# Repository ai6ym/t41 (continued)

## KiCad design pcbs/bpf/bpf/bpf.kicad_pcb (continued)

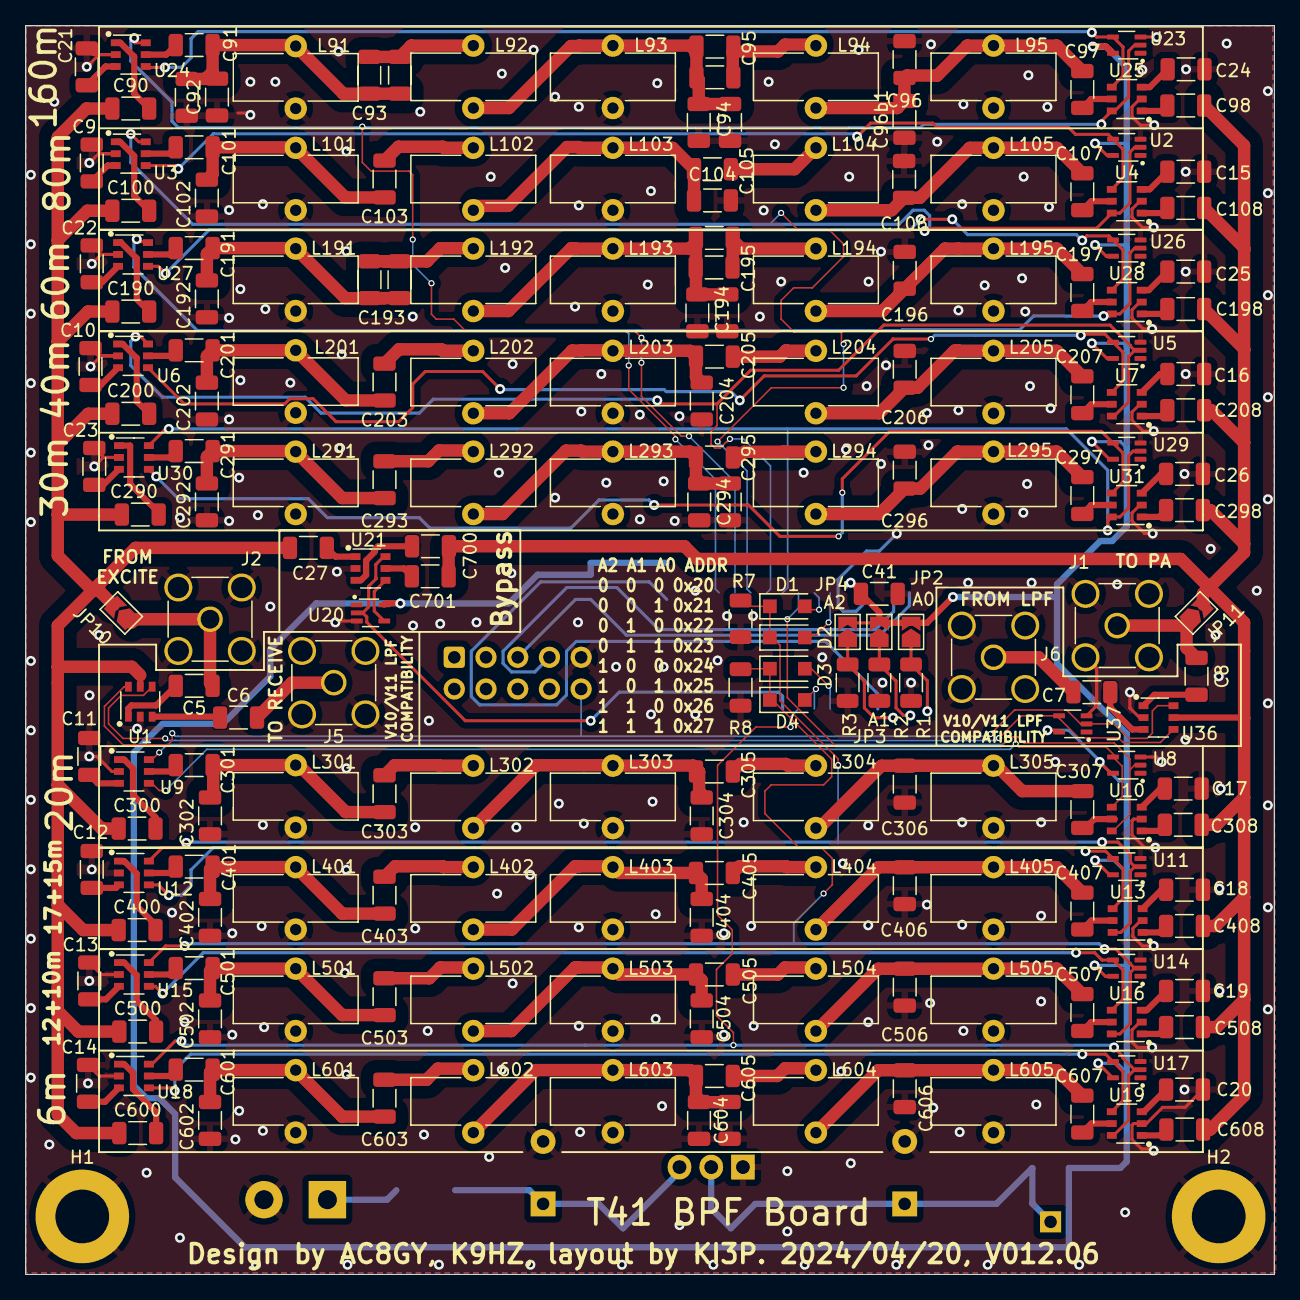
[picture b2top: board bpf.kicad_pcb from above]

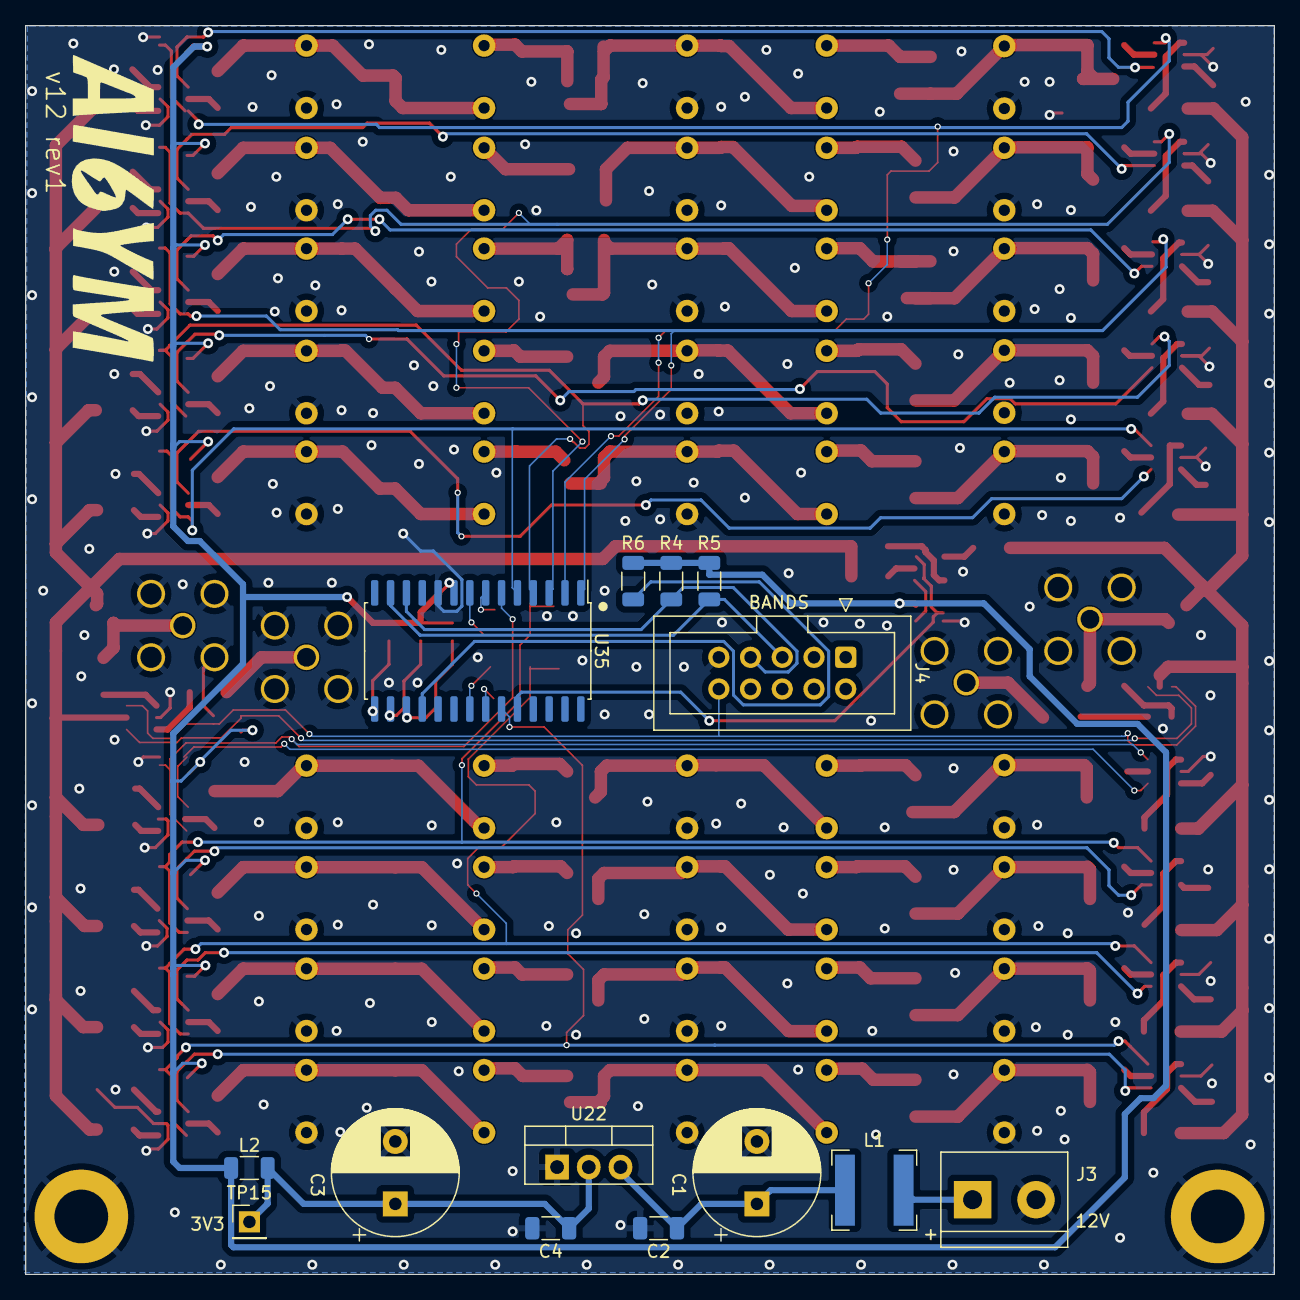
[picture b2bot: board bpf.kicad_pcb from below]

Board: 2 copper layers, 100.0 x 100.0 mm, 228 parts (14 on the bottom side), 149 nets.

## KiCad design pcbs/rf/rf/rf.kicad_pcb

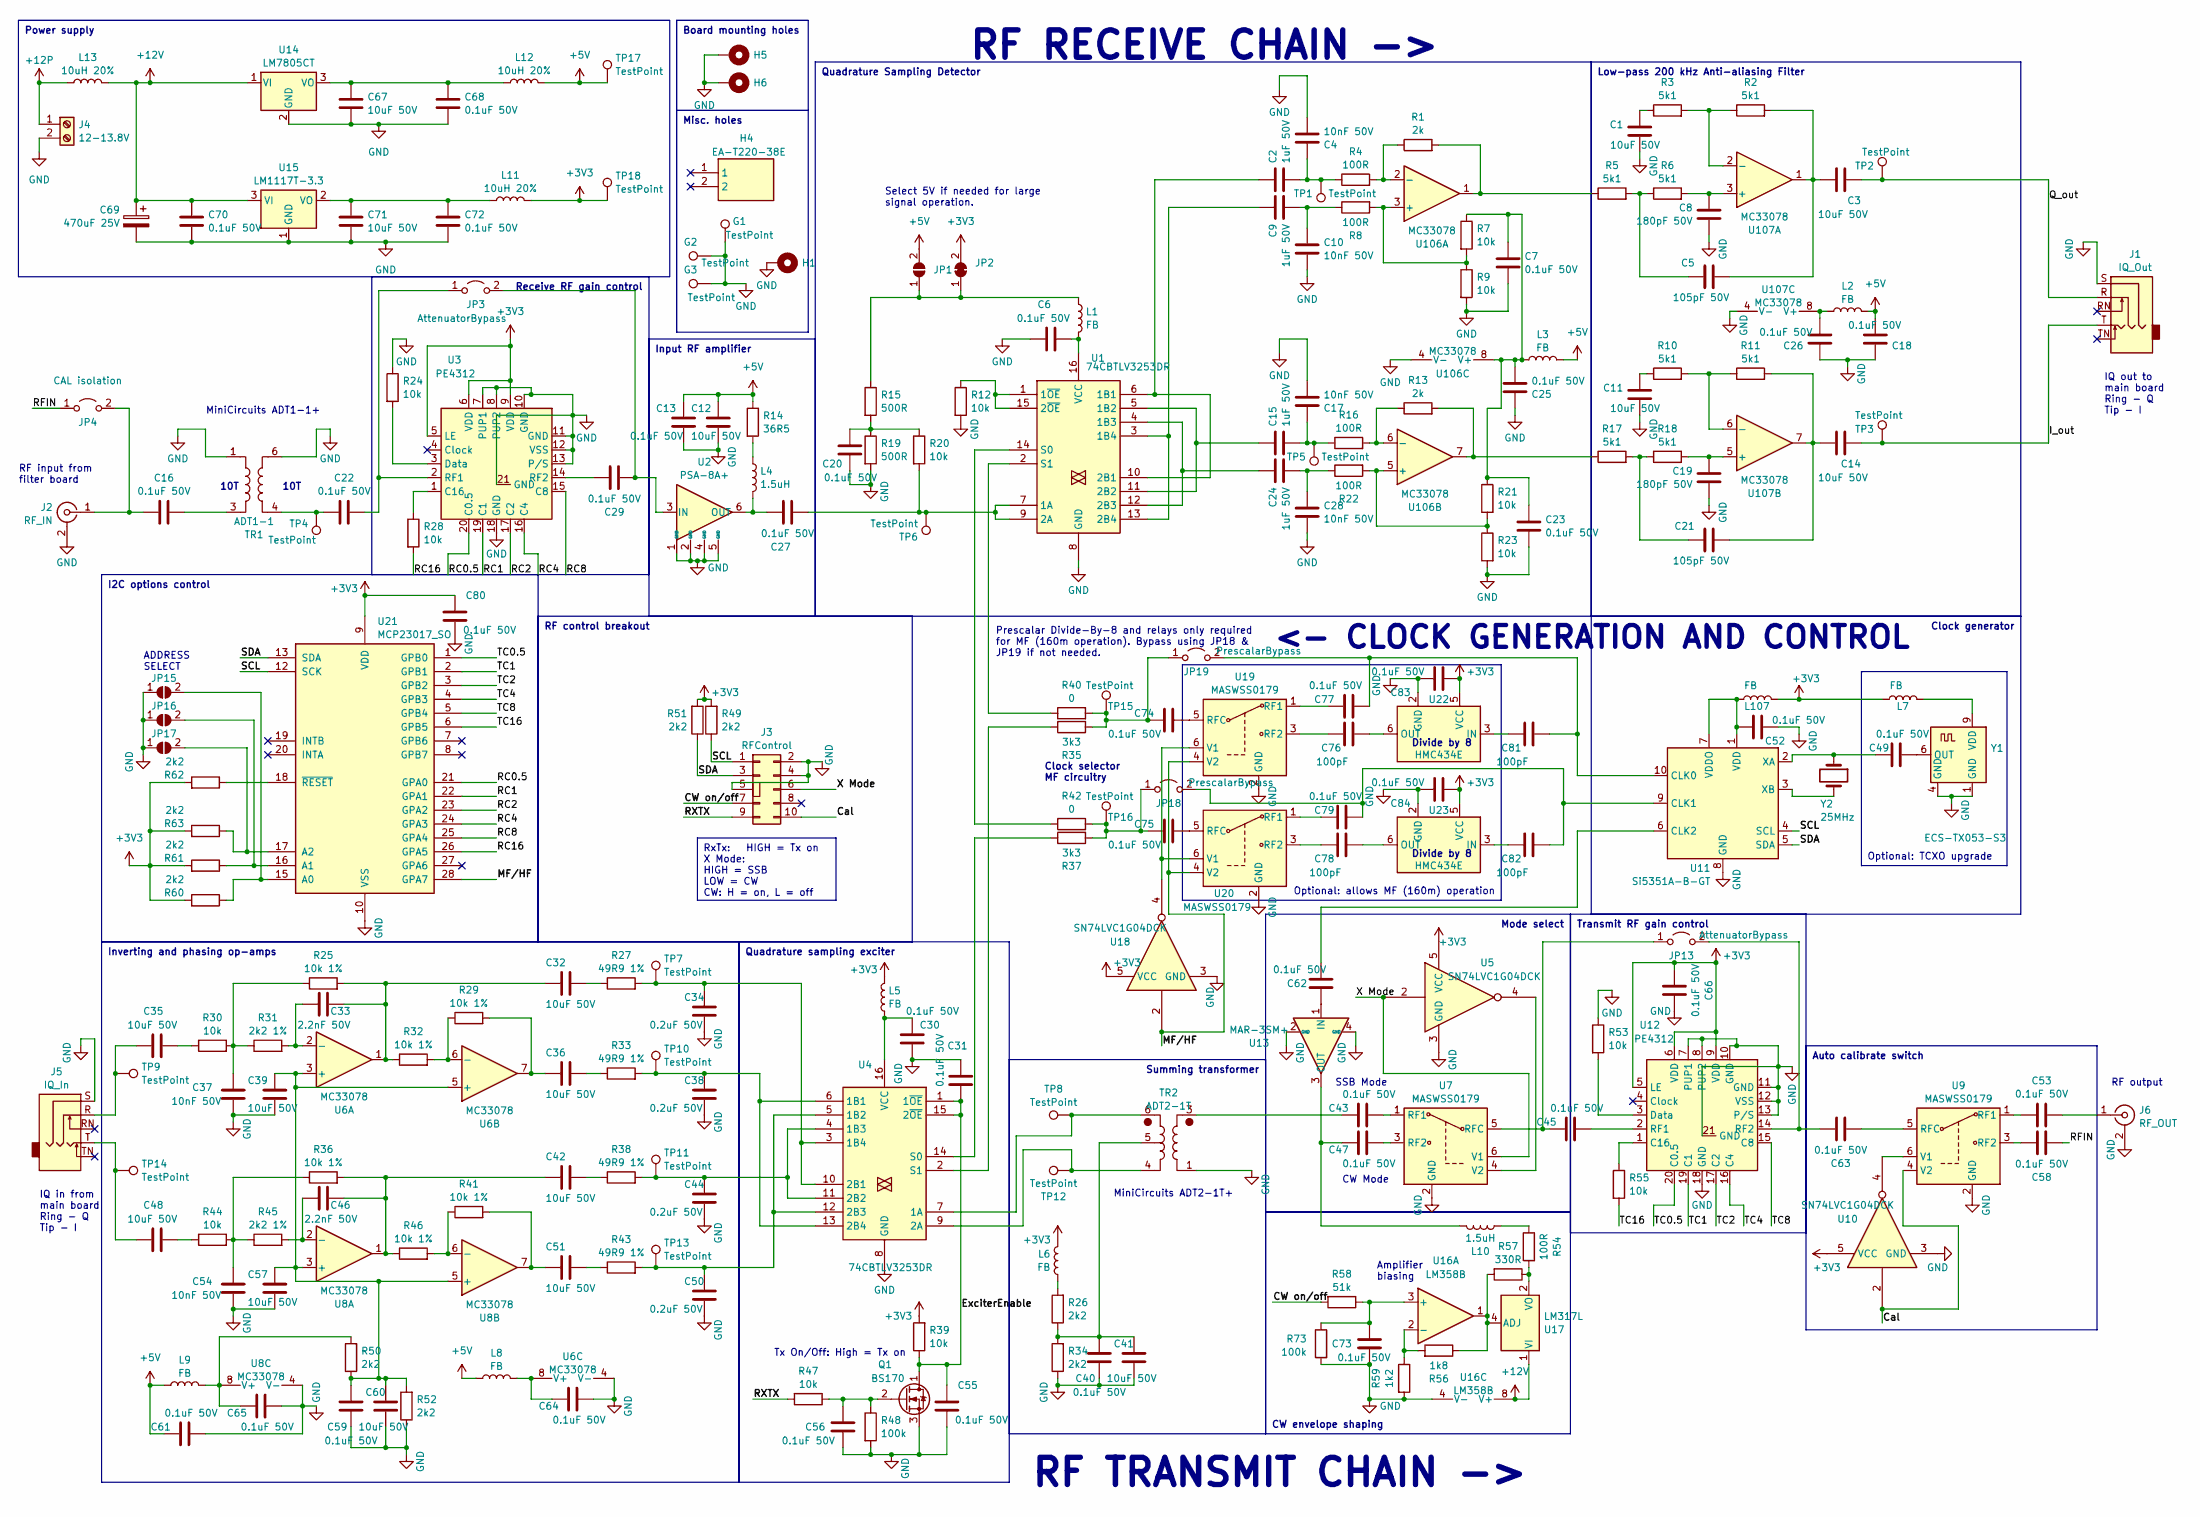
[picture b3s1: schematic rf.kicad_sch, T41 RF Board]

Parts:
C1, C3, C11, C12, C14, C32, C35, C36, C39, C41, C42, C48, C51, C57, C60, C67, C71: 10uF 50V; C_1206_3216Metric
C2, C9, C15, C24: 1uF 50V; C_1206_3216Metric
C4, C10, C17, C28, C37, C54: 10nF 50V; C_1206_3216Metric
C5, C21: 105pF 50V; C_1206_3216Metric
C6, C7, C13, C16, C18, C20, C22, C23, C25, C26, C27, C29, C30, C31, C40, C43, C45, C47, C49, C52, C53, C55, C56, C58, C59, C61, C62, C63, C64, C65, C66, C68, C70, C72, C73, C74, C75, C77, C79, C80, C83, C84: 0.1uF 50V; C_1206_3216Metric
C8, C19: 180pF 50V; C_1206_3216Metric
C33, C46: 2.2nF 50V; C_1206_3216Metric
C34, C38, C44, C50: 0.2uF 50V; C_1206_3216Metric
C69: 470uF 25V; CP_Radial_D10.0mm_P5.00mm
C76, C78, C81, C82: 100pF; C_1206_3216Metric
G1, G2, G3: TestPoint; PinHeader_1x01_P2.54mm_Vertical
H1: MountingHole_3.2mm_M3_Pad
H4: EA-T220-38E; EAT22038E; Mouser Part Number 588-EA-T220-38E
H5, H6: MountingHole_4.3mm_M4_DIN965_Pad
J1: IQ_Out; Jack_3.5mm_STX-3081_Horizontal
J2: RF_IN; SMA_Amphenol_901-144_Vertical; Mouser Part Number 712-CONSMA001-G
J3: RFControl; IDC-Header_2x05_P2.54mm_Vertical
J4: 12-13.8V; TerminalBlock_bornier-2_P5.08mm
J5: IQ_In; Jack_3.5mm_STX-3081_Horizontal
J6: RF_OUT; SMA_Amphenol_901-144_Vertical; Mouser Part Number 712-CONSMA001-G
JP1, JP15, JP16, JP17: SolderJumper_2_Open; SolderJumper-2_P1.3mm_Open_TrianglePad1.0x1.5mm
JP2: SolderJumper_2_Bridged; SolderJumper-2_P1.3mm_Bridged_RoundedPad1.0x1.5mm
JP3, JP13: AttenuatorBypass; PinHeader_1x02_P2.54mm_Vertical
JP4: CAL isolation; PinHeader_1x02_P2.54mm_Vertical
JP18, JP19: PrescalarBypass; PinHeader_1x02_P2.54mm_Vertical
L1, L2, L3, L5, L6, L7, L8, L9, L107: FB; R_1206_3216Metric
L4, L10: 1.5uH; R_1206_3216Metric
L11, L12, L13: 10uH 20%; L_Bourns-SRN6028
Q1: BS170; TO-92
R1, R13: 2k; R_1206_3216Metric
R2, R3, R5, R6, R10, R11, R17, R18: 5k1; R_1206_3216Metric
R4, R8, R16, R22, R54: 100R; R_1206_3216Metric
R7, R9, R12, R20, R21, R23, R24, R28, R30, R39, R44, R47, R53, R55: 10k; R_1206_3216Metric
R14: 36R5; R_1206_3216Metric
R15, R19: 500R; R_1206_3216Metric
R25, R29, R32, R36, R41, R46: 10k 1%; R_1206_3216Metric
R26, R34, R49, R50, R51, R52, R60, R61, R62, R63: 2k2; R_1206_3216Metric
R27, R33, R38, R43: 49R9 1%; R_1206_3216Metric
R31, R45: 2k2 1%; R_1206_3216Metric
R35, R37: 3k3; R_1206_3216Metric
R40, R42: 0; R_1206_3216Metric
R48, R73: 100k; R_1206_3216Metric
R56: 1k8; R_1206_3216Metric
R57: 330R; R_1206_3216Metric
R58: 51k; R_1206_3216Metric
R59: 1k2; R_1206_3216Metric
TP1, TP2, TP3, TP4, TP5, TP6, TP7, TP8, TP9, TP10, TP11, TP12, TP13, TP14, TP15, TP16, TP17, TP18: TestPoint; PinHeader_1x01_P2.54mm_Vertical
TR1: ADT1-1; Mini-Circuits_CD542_H2.84mm
TR2: ADT2-1T; Mini-Circuits_CD542_H2.84mm
U1, U4: 74CBTLV3253DR; SOIC-16_3.9x9.9mm_P1.27mm
U2: PSA-8A+; SOT-363_SC-70-6
U3, U12: PE4312; PE4312-QFN-20
U5, U10, U18: SN74LVC1G04DCK; SOT-SC70
U6, U8, U106, U107: MC33078; SOIC-8_3.9x4.9mm_P1.27mm
U7, U9, U19, U20: MASWSS0179; MASWSS0179-SOT-26
U11: Si5351A-B-GT; MSOP-10_3x3mm_P0.5mm
U13: MAR-3SM+; Mini-Circuits_WW107
U14: LM7805CT; TO-220-3_Vertical
U15: LM1117T-3.3; TO-220-3_Vertical
U16: LM358B; SOIC-8_3.9x4.9mm_P1.27mm
U17: LM317L; SOIC-8_3.9x4.9mm_P1.27mm
U21: MCP23017_SO; SOIC-28W_7.5x17.9mm_P1.27mm
U22, U23: HMC434E; SOT-23-6
Y1: ECS-TX053-S3; Oscillator_ECS_TXO53_S3
Y2: 25MHz; Crystal_SMD_HC49-SD_HandSoldering

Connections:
+3V3: C66.2, C80.2, C83.1, C84.1, JP2.2 (B), L5.1, L6.1, L7.2, L11.2, L107.1, R39.2, R49.2, R51.2, R60.2, R61.2, R62.2, R63.2, TP18.1, U3.5 (LE), U3.6 (VDD), U3.9 (VDD), U5.5 (VCC), U10.5 (VCC), U12.5 (LE), U12.6 (VDD), U12.9 (VDD), U18.5 (VCC), U21.9 (VDD), U22.5 (VCC), U23.5 (VCC)
+5V: C12.2, C13.2, C18.1, C61.1, JP1.2 (B), L2.2, L3.2, L8.2, L9.2, L12.2, R14.1, TP17.1
+12V: C69.1, C70.1, L13.2, U14.1 (VI), U15.3 (VI), U16.8 (V+), U17.1 (VI)
/CW on/off: J3.7, R58.2
/Cal: J3.10, U9.4 (V2), U10.2
/ExciterEnable: C31.1, C55.2, Q1.1 (D), R39.1, U4.1 (1~OE), U4.15 (2~OE)
/I_out: C14.1, J1.T, TP3.1
/MF/HF: U18.2, U19.4 (V2), U20.4 (V2), U21.28 (GPA7)
/Q_out: C3.1, J1.R, TP2.1
/RC0.5: U3.20 (C0.5), U21.21 (GPA0)
/RC1: U3.19 (C1), U21.22 (GPA1)
/RC2: U3.17 (C2), U21.23 (GPA2)
/RC4: U3.16 (C4), U21.24 (GPA3)
/RC8: U3.15 (C8), U21.25 (GPA4)
/RC16: R28.2, U21.26 (GPA5)
/RFIN: C58.2, JP4.1 (A)
/RXTX: J3.9, R47.2
/SCL: J3.1, R49.1, U11.4 (SCL), U21.12 (SCK)
/SDA: J3.3, R51.1, U11.5 (SDA), U21.13 (SDA)
/TC0.5: U12.20 (C0.5), U21.1 (GPB0)
/TC1: U12.19 (C1), U21.2 (GPB1)
/TC2: U12.17 (C2), U21.3 (GPB2)
/TC4: U12.16 (C4), U21.4 (GPB3)
/TC8: U12.15 (C8), U21.5 (GPB4)
/TC16: R55.2, U21.6 (GPB5)
/X Mode: J3.6, U5.2, U7.6 (V1)
GND: C1.1, C4.1, C6.1, C7.1, C8.1, C10.1, C11.1, C12.1, C13.1, C17.1, C18.2, C19.1, C20.1, C23.1, C25.2, C26.2, C28.1, C30.1, C31.2, C34.2, C37.2, C38.2, C39.2, C40.1, C41.2, C44.2, C50.2, C52.2, C54.2, C55.1, C56.1, C57.2, C59.1, C60.2, C61.2, C64.2, C65.2, C66.1, C67.2, C68.2, C69.2, C70.2, C71.2, C72.2, C73.1, C80.1, C83.2, C84.2, G1.1, G2.1, G3.1, H1.1, H5.1, H6.1, J1.S, J2.2 (Ext), J3.2, J3.4, J3.5, J4.2, J5.S, J6.2 (Ext), JP15.1 (A), JP16.1 (A), JP17.1 (A), Q1.3 (S), R9.2, R12.2, R19.2, R23.2, R24.1, R34.1, R48.2, R52.1, R53.1, R59.2, R73.2, TR1.1, TR1.6, TR2.1, U1.8 (GND), U2.1 (GND), U2.2 (GND), U2.4 (GND), U2.5 (GND), U3.7 (PUP1), U3.8 (PUP2), U3.10 (GND), U3.11 (GND), U3.12 (VSS), U3.13 (P/S), U3.18 (GND), U3.21 (GND), U4.8 (GND), U5.3 (GND), U6.4 (V-), U7.2 (GND), U8.4 (V-), U9.2 (GND), U10.3 (GND), U11.8 (GND), U12.7 (PUP1), U12.8 (PUP2), U12.10 (GND), U12.11 (GND), U12.12 (VSS), U12.13 (P/S), U12.18 (GND), U12.21 (GND), U13.2 (GND), U13.4 (GND), U14.2 (GND), U15.1 (GND), U16.4 (V-), U18.3 (GND), U19.2 (GND), U20.2 (GND), U21.10 (VSS), U22.2 (GND), U23.2 (GND), U106.4 (V-), U107.4 (V-), Y1.1 (GND), Y1.4 (GND)
unnamed: C1.2, R3.1
unnamed: C2.1, C4.2, R4.1, TP1.1
unnamed: C3.2, C5.1, R2.2, U107.1
unnamed: C5.2, R5.2, R6.1
unnamed: C9.1, C10.2, R8.1
unnamed: C11.2, R10.1
unnamed: C14.2, C21.1, R11.2, U107.7
unnamed: C15.1, C17.2, R16.1, TP5.1
unnamed: C16.2, TR1.3
unnamed: C20.2, R15.2, R19.1, R20.1
unnamed: C21.2, R17.2, R18.1
unnamed: C22.1, TP4.1, TR1.4
unnamed: C24.1, C28.2, R22.1
unnamed: C32.1, C33.1, R25.2, R32.1, U6.1
unnamed: C32.2, R27.1
unnamed: C35.1, R30.1
unnamed: C35.2, J5.R, TP9.1
unnamed: C36.1, R29.2, U6.7
unnamed: C36.2, R33.1
unnamed: C37.1, R25.1, R30.2, R31.1
unnamed: C40.2, C41.1, R26.1, R34.2, TR2.5
unnamed: C42.1, C46.1, R36.2, R46.1, U8.1
unnamed: C42.2, R38.1
unnamed: C43.1, TR2.3
unnamed: C48.1, R44.1
unnamed: C48.2, J5.T, TP14.1
unnamed: C51.1, R41.2, U8.7
unnamed: C51.2, R43.1
unnamed: C54.1, R36.1, R44.2, R45.1
unnamed: C16.1, J2.1 (In), JP4.2 (B)
unnamed: J4.1, L13.1
unnamed: C53.2, J6.1 (In)
unnamed: JP1.1 (A), JP2.1 (A), L1.1, R15.1
unnamed: C22.2, JP3.1 (A), U3.2 (RF1)
unnamed: C29.2, JP3.2 (B), U2.3 (IN)
unnamed: C45.1, JP13.1 (A), U7.5 (RFC)
unnamed: C63.1, JP13.2 (B), U12.14 (RF2)
unnamed: JP15.2 (B), R60.1, U21.15 (A0)
unnamed: JP16.2 (B), R61.1, U21.16 (A1)
unnamed: JP17.2 (B), R63.1, U21.17 (A2)
unnamed: C75.2, JP18.1 (A), R37.2, R42.2, TP16.1
unnamed: C79.1, C82.1, JP18.2 (B), U11.9 (CLK1)
unnamed: C74.2, JP19.1 (A), R35.2, R40.2, TP15.1
unnamed: C77.1, C81.1, JP19.2 (B), U11.10 (CLK0)
unnamed: L4.1, R14.2
unnamed: L6.2, R26.2
unnamed: L10.1, R54.1
unnamed: C56.2, Q1.2 (G), R47.1, R48.1
unnamed: R1.2, R5.1, U106.1
unnamed: R13.2, R17.1, U106.7
unnamed: R54.2, R57.1, U17.2 (VO), U17.3 (VO), U17.6 (VO), U17.7 (VO)
unnamed: C27.2, R20.2, TP6.1, U1.7 (1A), U1.9 (2A)
unnamed: C2.2, U1.6 (1B1), U1.10 (2B1)
unnamed: C15.2, U1.5 (1B2), U1.11 (2B2)
unnamed: C24.2, U1.4 (1B3), U1.12 (2B3)
unnamed: C9.2, U1.3 (1B4), U1.13 (2B4)
unnamed: R12.1, U1.1 (1~OE), U1.15 (2~OE)
unnamed: R42.1, U1.14 (S0)
unnamed: R40.1, U1.2 (S1)
unnamed: C6.2, L1.2, U1.16 (VCC)
unnamed: C27.1, L4.2, U2.6 (OUT)
unnamed: R28.1, U3.1 (C16)
unnamed: R24.2, U3.3 (Data)
unnamed: C29.1, U3.14 (RF2)
unnamed: TP8.1, TR2.6, U4.7 (1A)
unnamed: C38.1, R33.2, TP10.1, U4.6 (1B1), U4.13 (2B4)
unnamed: C50.1, R43.2, TP13.1, U4.5 (1B2), U4.12 (2B3)
unnamed: C44.1, R38.2, TP11.1, U4.4 (1B3), U4.11 (2B2)
unnamed: C34.1, R27.2, TP7.1, U4.3 (1B4), U4.10 (2B1)
unnamed: TP12.1, TR2.4, U4.9 (2A)
unnamed: R37.1, U4.14 (S0)
unnamed: R35.1, U4.2 (S1)
unnamed: C30.2, L5.2, U4.16 (VCC)
unnamed: C39.1, C57.1, C59.2, C60.1, R50.1, R52.2, U6.3 (+), U6.5 (+), U8.3 (+), U8.5 (+)
unnamed: C33.2, R31.2, U6.2 (-)
unnamed: R29.1, R32.2, U6.6 (-)
unnamed: C64.1, L8.1, U6.8 (V+)
unnamed: C43.2, U7.1 (RF1)
unnamed: C47.2, U7.3 (RF2)
unnamed: U5.4, U7.4 (V2)
unnamed: C46.2, R45.2, U8.2 (-)
unnamed: R41.1, R46.2, U8.6 (-)
unnamed: C65.1, L9.1, R50.2, U8.8 (V+)
unnamed: C53.1, U9.1 (RF1)
unnamed: C58.1, U9.3 (RF2)
unnamed: C63.2, U9.5 (RFC)
unnamed: U9.6 (V1), U10.4
unnamed: C62.2, U11.6 (CLK2)
unnamed: C52.1, L107.2, U11.1 (VDD), U11.7 (VDDO)
unnamed: C49.1, U11.2 (XA), Y2.1
unnamed: U11.3 (XB), Y2.2
unnamed: R55.1, U12.1 (C16)
unnamed: R53.2, U12.3 (Data)
unnamed: C45.2, U12.2 (RF1)
unnamed: C62.1, U13.1 (IN)
unnamed: C47.1, L10.2, U13.3 (OUT)
unnamed: C67.1, C68.1, L12.1, U14.3 (VO)
unnamed: C71.1, C72.1, L11.1, U15.2 (VO)
unnamed: C73.2, R58.1, R73.1, U16.3 (+)
unnamed: R56.2, R59.1, U16.2 (-)
unnamed: R56.1, R57.2, U16.1, U17.4 (ADJ)
unnamed: C77.2, U19.1 (RF1)
unnamed: C76.2, U19.3 (RF2)
unnamed: C74.1, U19.5 (RFC)
unnamed: U18.4, U19.6 (V1), U20.6 (V1)
unnamed: C79.2, U20.1 (RF1)
unnamed: C78.2, U20.3 (RF2)
unnamed: C75.1, U20.5 (RFC)
unnamed: R62.1, U21.18 (~RESET)
unnamed: C81.2, U22.3 (IN)
unnamed: C76.1, U22.6 (OUT)
unnamed: C82.2, U23.3 (IN)
unnamed: C78.1, U23.6 (OUT)
unnamed: R7.2, R8.2, R9.1, U106.3 (+)
unnamed: R1.1, R4.2, U106.2 (-)
unnamed: R21.2, R22.2, R23.1, U106.5 (+)
unnamed: R13.1, R16.2, U106.6 (-)
unnamed: C7.2, C23.2, C25.1, L3.1, R7.1, R21.1, U106.8 (V+)
unnamed: C8.2, R6.2, U107.3 (+)
unnamed: R2.1, R3.2, U107.2 (-)
unnamed: C19.2, R18.2, U107.5 (+)
unnamed: R10.2, R11.1, U107.6 (-)
unnamed: C26.1, L2.1, U107.8 (V+)
unnamed: C49.2, Y1.6 (OUT)
unnamed: L7.1, Y1.9 (VDD)

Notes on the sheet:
RF control breakout
Auto calibrate switch
Power supply
Optional: TCXO upgrade
Mode select
Inverting and phasing op-amps
Transmit RF gain control
Input RF amplifier
Low-pass 200 kHz Anti-aliasing Filter
Clock generator
Summing transformer
I2C options control
RxTx: HIGH = Tx on X Mode: HIGH = SSB LOW = CW CW: H = on, L = off
Quadrature sampling exciter
Optional: allows MF (160m) operation
Quadrature Sampling Detector
Receive RF gain control
Misc. holes
CW envelope shaping
Board mounting holes
RF output
RF input from filter board
Amplifier biasing
<- CLOCK GENERATION AND CONTROL
Clock selector MF circuitry
IQ out to main board Ring - Q Tip - I
CW Mode
10T
RF RECEIVE CHAIN ->
Divide by 8
Select 5V if needed for large signal operation.
ADDRESS SELECT
Tx On/Off: High = Tx on
SSB Mode
IQ in from main board Ring - Q Tip - I
Prescalar Divide-By-8 and relays only required for MF (160m operation). Bypass using JP18 & JP19 if not needed.
MiniCircuits ADT2-1T+
MiniCircuits ADT1-1+
RF TRANSMIT CHAIN ->

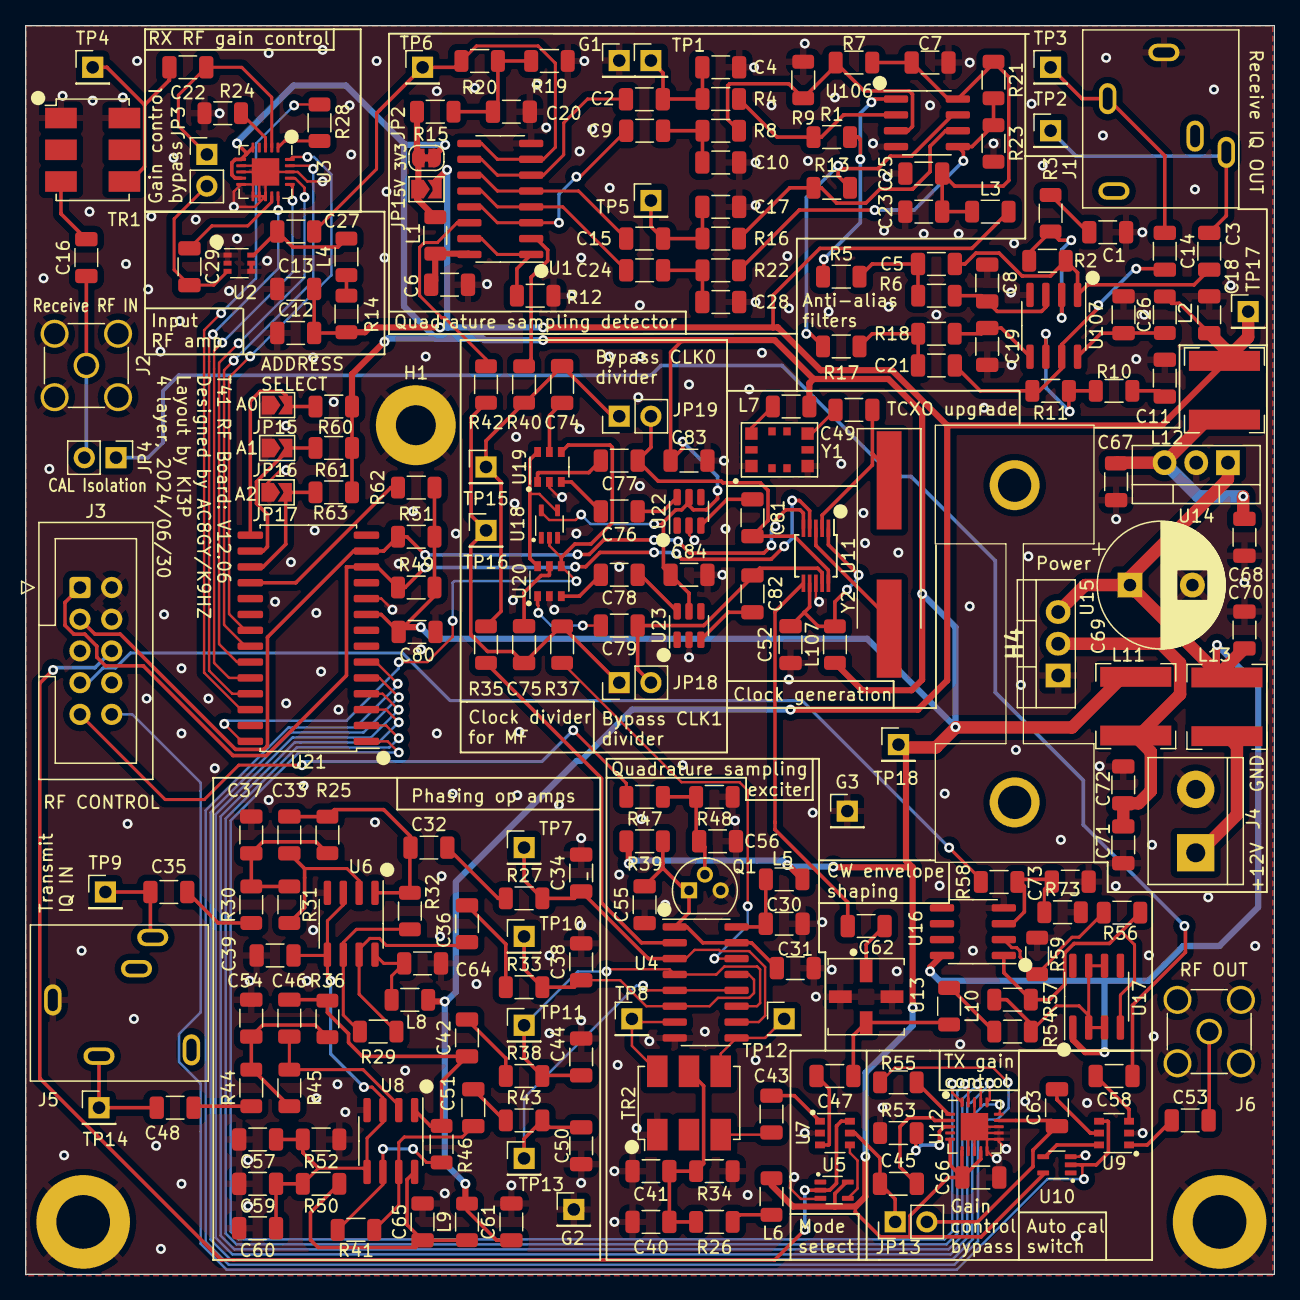
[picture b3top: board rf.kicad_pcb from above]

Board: 4 copper layers, 100.0 x 100.0 mm, 233 parts (0 on the bottom side), 152 nets.

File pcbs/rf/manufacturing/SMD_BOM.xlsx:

|  |  | xxxx xxxx xxxxx xxPCS BOM (Sample Bill of Materials)
Item # | *Designator | *Qty | Manufacturer | *Mfg Part # | Description / Value | *Package/Footprint | Type | Your Instructions / Notes
1 | C1, C3, C11, C12, C14, C32, C35, C36, C39, C41, C42, C48, C51, C57, C60, C67, C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 | 17 | Kyocera AVX | 12065D106KAT2A | 10uF 50V SMD 1206 Capacitor | 1206 | SMD
2 | C2, C9, C15, C24 | 4 | Samsung Electro-Mechanics | CL31B105KBHNNNE | 1uF 50V SMD 1206 Capacitor | 1206 | SMD
3 | C4, C10, C17, C28, C37, C54 | 6 | KEMET | C1206C103K5RAC7210 | 10nF 50V SMD 1206 Capacitor | 1206 | SMD
4 | C5, C21 | 2 | Kyocera AVX | 12065C101KAT2A | 100pF 50V SMD 1206 Capacitor | 1206 | SMD
5 | C8, C19 | 2 | Walsin | 1206B181K160CT | 180pF 50V SMD 1206 Capacitor | 1206 | SMD
6 | C6, C7, C13, C16, C18, C20, C22, C23, C25, C26, C27, C29, C30, C31, C40, C43, C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 | 36 | KEMET | C1206C104K5RACTU | 0.1uF 50V SMD 1206 Capacitor | 1206 | SMD
7 | C33, C46 | 2 | KEMET | C1206C222K5RAC | 2.2nF 50V SMD 1206 Capacitor | 1206 | SMD
8 | C34, C38, C44, C50 | 4 | Kyocera AVX | 12065C204KAT4A | 0.2uF 50V SMD 1206 Capacitor | 1206 | SMD
9 | L1, L2, L3, L5, L6, L7, L8, L9, L107 | 9 | Laird Performance Materials | HZ1206E601R-10 | FB SMD 1206 600 Ohm 1A | 1206 | SMD
10 | L4, L10 | 2 | Murata Electronics | LQM31PN1R5M00L | 1.5uH SMD 1206 Inductor | 1206 | SMD
11 | L11, L12, L13 | 3 | Murata Electronics | 1264EY-100M=P3 | 10uH 20% SMD Inductor | 6.3mm x 6.3mm | SMD
12 | R1, R13 | 2 | Panasonic | ERA-8AEB202V | 2K Ohm SMD 1206 Resistor | 1206 | SMD
13 | R2, R3, R5, R6, R10, R11, R17, R18 | 8 | Bourns | CR1206-JW-512ELF | 5.1K Ohm SMD 1206 Resistor | 1206 | SMD
14 | R4, R8, R16, R22, R54 | 5 | Bourns | CR1206-FX-1000ELF | 100 Ohm SMD 1206 Resistor | 1206 | SMD
15 | R7, R9, R12, R20, R21, R23, R24, R28, R30, R39, R44, R47, R53, R55 | 14 | Bourns | CR1206-JW-103ELF | 10K Ohm SMD 1206 Resistor | 1206 | SMD
16 | R14 | 1 | Vishay / Dale | CRCW120636R5FKEA | 36.5 Ohm SMD 1206 Resistor | 1206 | SMD
17 | R15, R19 | 2 | Bourns | CR1206-FX-5100ELF | 510 Ohm SMD 1206 Resistor | 1206 | SMD
18 | R25, R29, R32, R36, R41, R46 | 6 | Bourns | CR1206-FX-1002ELF | 10K Ohm 1% SMD 1206 Resistor | 1206 | SMD
19 | R26, R34, R49, R50, R51, R52, R60, R61, R62, R63 | 10 | Vishay / Dale | CRCW12062K20JNEAC | 2.2K Ohm SMD 1206 Resistor | 1206 | SMD
20 | R27, R33, R38, R43 | 4 | Vishay / Dale | CRCW120649R9FKEAC | 49.9 Ohm 1% SMD 1206 Resistor | 1206 | SMD
21 | R31, R45 | 2 | Bourns | CR1206-FX-2201ELF | 2.2K Ohm 1% SMD 1206 Resistor | 1206 | SMD
22 | R35, R37 | 2 | Vishay / Dale | CRCW12063K30FKEA | 3.3K Ohm SMD 1206 Resistor | 1206 | SMD
23 | R40, R42 | 2 | Vishay / Dale | CRCW12060000Z0EAC | 0 Ohm SMD 1206 Resistor | 1206 | SMD
24 | R48, R73 | 2 | Vishay / Dale | CRCW1206100KFKEAC | 100K Ohm SMD 1206 Resistor | 1206 | SMD
25 | R56 | 1 | Bourns | CR1206-FX-1801ELF | 1.8K Ohm SMD 1206 Resistor | 1206 | SMD
26 | R57 | 1 | Bourns | CR1206-FX-3300ELF | 330 Ohm SMD 1206 Resistor | 1206 | SMD
27 | R58 | 1 | Bourns | CR1206-FX-5102ELF | 51K Ohm SMD 1206 Resistor | 1206 | SMD
28 | R59 | 1 | Bourns | CR1206-FX-1201ELF | 1.2K Ohm SMD 1206 Resistor | 1206 | SMD
29 | U1, U4 | 2 | Texas Instruments | SN74CBTLV3253DR | 74CBTLV3253DR in SOIC-16 | 16-SOIC | SMD
30 | U2 | 1 | Mini-Circuits | PSA-8A+ | PSA-8A+ | CA1389 | SMD
31 | U3, U12 | 2 | pSemi | PE4312C-Z | PE4312 (or DAT-31R5A-PP+) | QFN-20 | SMD
32 | U5, U10 | 2 | Texas Instruments | SN74LVC1G04DCKR | 74LVC1G04DCKR | SC70-5 | SMD
33 | U6, U8, U106, U107 | 4 | Texas Instruments | MC33078DR | MC33078 | SOIC-8 | SMD
34 | U16 | 1 | Texas Instruments | LM358BIDR | LM358B | SOIC-8 | SMD
35 | U7, U9 | 2 | Macom | MASWSS0179TR-3000 | MASWSS0179 | SOT-26 | SMD
36 | U11 | 1 | Skyworks Solutions, Inc. | SI5351A-B-GT | Si5351A-B-GT | MSOP-10 | SMD
37 | U13 | 1 | Mini-Circuits | MAR-3SM+ | MAR-3SM+ | WW107 | SMD
38 | U17 | 1 | Texas Instruments | LM317LIDR | LM317LIDR | SOIC-8 | SMD
39 | U21 | 1 | Microchip Technology | MCP23017-E/SO | MCP23017_SO | SOIC-28 | SMD
40 | TR1 | 1 | Mini-Circuits | ADT1-1+ | ADT1-1+ | CD542 | SMD
41 | TR2 | 1 | Mini-Circuits | ADT2-1T+ | ADT2-1T+ | CD542 | SMD
42 | Y1 | 1 | ECS | ECS-TXO53-S3-33-250-BN-TR | ECS-TX053-S3 | 5.0 x 3.2 mm | SMD
43 | Y2 | 1 | ECS | ECS-250-18-5PX-GM-TR | 25MHz | SPX | SMD
Need a quick and accurante quote? Need an efficient production? Please read SMT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
Click for Instructions on How to Create a BOM

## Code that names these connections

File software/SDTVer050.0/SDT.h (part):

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
//======================================== User section that might need to be changed ===================================
#include "MyConfigurationFile.h"                                          // This file name should remain unchanged
#define VERSION                     "V050.0"                              // Change this for updates. If you make this longer than 9 characters, brace yourself for surprises
#define UPDATE_SWITCH_MATRIX        0                                     // 1 = Yes, redo the switch matrix values, 0 = leave switch matrix values as is from the last change
struct maps {
  char mapNames[50];
  float lat;
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#include <util/crc16.h>                             // mdrhere
#include <utility/imxrt_hw.h>                       // for setting I2S freq, Thanks, FrankB!
#include <EEPROM.h>
//======================================== Symbolic Constants for the T41 ===================================================
#define RIGNAME                     "T41-EP SDT"
#if defined(G0ORX_FRONTPANEL_2)
#define NUMBER_OF_SWITCHES          20              // Number of push button switches. 16 on older boards
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#define SD_CS                       BUILTIN_SDCARD  // Works on T_3.6 and T_4.1 ...
#define MAX_SD_ITEMS                184             // Number of discrete data items written to EEPROM

//#define STORE_SWITCH_VALUES                       // Uncomment to save the analog switch values for your push button matrix

#define OFF                         0
#define ON                          1
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
//======================================== Symbolic constants ==========================================================

// These constants are used by the voltage divider network so only 1 analog pin is used for the 16 option switches. These may need
// to be changed for the exact value for your system. They are initialized in the INO file.

#define BUSY_ANALOG_PIN              39     // This is the analog pin that controls the 18 switches
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
#define WIGGLE_ROOM                  20     // This is the maximum value that can added to a BUSY_ANALOG_PIN pin read value of a push
//                                             button and still have the switch value be associated with the correct push button.
#define SWITCH_DEBOUNCE_DELAY       50L     // Milliseconds for the switch to settle down
#define AUDIO_PLOT_CEILING          119     // (SPECTRUM_BOTTOM - AUDIO_SPECTRUM_TOP)

#define MAX_FAVORITES                13     // Max number of favorite frequencies stored in EEPROM

#define PRIMARY_MENU                  0
#define SECONDARY_MENU                1
#define SELECTED_INDEX                3     // This is the index for MENU_OPTION_SELECT
#define PRIMARY_MENU_X                0
#define SECONDARY_MENU_X              250
#define MENUS_Y                       0
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#define BOTH_MENU_WIDTHS             (EACH_MENU_WIDTH * 2 + 30)


#define MENU_OPTION_SELECT           0     // Switches changed for new menu system JJP 3/10/24
#define MAIN_MENU_UP                 1
#define BAND_UP                      2
#define ZOOM                         3
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#define BEARING                     17    // AFP 10-11-22
*/
//=======================================================
#define XPIXELS                     800           // This is for the 5.0" display
#define YPIXELS                     480
#define PIXELHEIGHT                  20           // Used in fillRec() to erase a line
#define CHAR_HEIGHT                  32
#define PIXELS_PER_EQUALIZER_DELTA   10           // Number of pixeks per detent of encoder for equalizer changes
#define PIXELS_PER_AUDIO_DELTA       10

#define SPECTRUM_LEFT_X       3            // Used to plot left edge of spectrum display  AFP 12-14-21
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#define SMETER_BAR_HEIGHT     18
#define SMETER_BAR_LENGTH     180
#define SPECTRUM_NOISE_FLOOR  (SPECTRUM_TOP_Y + SPECTRUM_HEIGHT - 3)
#define TIME_X                (XPIXELS * 0.83)                            // Upper-left corner for time --G0ORX
#define TIME_Y                (YPIXELS * 0.07)
#define WHICH_SIDEBAND_X      (XPIXELS * 0.70)
#define WHICH_SIDEBAND_Y      (YPIXELS * 0.20)
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#define FREQUENCY_PIXEL_HI    45
#define SPLIT_INCREMENT       500L
//                                                            Offsets for status info
#define FIELD_OFFSET_X        WATERFALL_RIGHT_X + 118                     // X coordinate for field
#define NOTCH_X               WATERFALL_RIGHT_X + 58
#define NOTCH_Y               WATERFALL_TOP_Y   + 90
#define NOISE_REDUCE_X        WATERFALL_RIGHT_X + 58
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#define HISTOGRAM_ELEMENTS      750
#define LOWEST_ATOM_TIME         20                   // 60WPM has an atom of 20ms
#define HIGHEST_ATOM_TIME       240                   // 5WPM has an atom of 240ms                              
#define DIT_WEIGHT              0.3                   // Previous values account for 90% of average
#define AVERAGE_DIT_WEIGHT      0.7                   // The number above and this one must equal 1.0
#define DITLENGTH_OBSERVATIONS  10                    // Number of ditlength observations to compute average
#define ADAPTIVE_SCALE_FACTOR   0.8                   // The amount of old histogram values are presesrved
#define SCALE_CONSTANT          (1.0 / (1.0 - ADAPTIVE_SCALE_FACTOR)) // Insure array has enough observations to scale
#define FILTER_WIDTH            25                    // The default filter highlight in spectrum displah
#define ZOOM_2X_BIN_COUNT       187.5                 // The 2x bin count for display
#define MAX_AUDIO_VOLUME        100
#define MIN_AUDIO_VOLUME         16                   //yours might be different. On my rig, this is where the band noise disappears.

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
#define DO_NOTHING              -1

#define FLOAT_PRECISION          6                 // Assumed precision for a float
#define BUFFER_SINE_COUNT        8                 // Leads to a 750Hz signal

#define EQUALIZER_CELL_COUNT    14
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#define NOISE_SAMPLE_SIZE         500
#define SD_MULTIPLIER             3
#define NOISE_MULTIPLIER          0.5         // Signal must be this many time greater than the noise floor
#define STARTING_DITLENGTH        80          // dit length for 15wpm

#define  BLACK                    0x0000      /*   0,   0,   0 */
#define  RA8875_BLUE              0x000F      /*   0,   0, 128 */
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#include <utility/imxrt_hw.h> // for setting I2S freq, Thanks, FrankB!
#define WFM_SAMPLE_RATE             256000.0f

//#define TIMEZONE                    "EST: "     // Set for eastern time

//#define DEFAULTFREQINCREMENT        1000L       //Values 10, 50, 100, 250, 1000, 10000  AFP 09-26-22
//#define FAST_TUNE_INCREMENT         50L
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//#define FREQ_SEP_CHARACTER          ','

//========================================================= Pin Assignments =====================================
//========================================= Pins 0 and 1 are usually reserved for the USB COM port communications
//========================================= On the Teensy 4.1 board, pins GND, 0-12, and pins 13-23, 3.3V, GND, and
//========================================= Vin are "covered up" by the Audio board. However, not all of those pins are
//========================================= actually used by the board. See: https://www.pjrc.com/store/teensy3_audio.html
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#define FILTERPIN40M                31    // 40M filter relay
#define FILTERPIN20M                28    // 20M filter relay
#define FILTERPIN15M                29    // 15M filter relay
#define RXTX                        22    // Transmit/Receive
#define PTT                         37    // Transmit/Receive
#define MUTE                        38    // Mute Audio,  HIGH = "On" Audio available from Audio PA, LOW = Mute audio
//========================================= Switch pins
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#define MENU_MINUS                  106    // Menu decrement
#define MENU_PLUS                   107    // this is the menu button pin
#define CHANGE_NOISE                108    // this is the pushbutton pin of NR
#define CHANGE_DEMOD                109    // this is the push button for demodulation
#define CHANGE_ZOOM                 110    // Push button for display zoom feature
#define SET_FREQ_CURSOR             111    // Push button for frequency Cursor feature  was 39 for Al

#define NO_MENUS_ACTIVE             0      // No menus displayed 
#define PRIMARY_MENU_ACTIVE         1      // A primary menu is active
#define SECONDARY_MENU_ACTIVE       2      // Both primary and secondary menus active

//========================================= Keyer pins
#define KEYER_DAH_INPUT_RING         35    // Ring connection for keyer  -- default for righthanded user
#define KEYER_DIT_INPUT_TIP          36    // Tip connection for keyer

#define OPTO_OUTPUT                  24    // To optoisolator and keyed circuit
#define STRAIGHT_KEY                  0
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//#define CONFIG_VERSION              "mr1"             //mdrhere ID of the E settings block, change if structure changes
//#define CONFIG_START 0                                // Address start the EEPROM data. (emulated with size of 4K. Actual address managed in library)
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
